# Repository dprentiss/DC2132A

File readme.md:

#DC Bench Power Supply#

Project Features:

- Based on Linear Technology's demostration circuit, [DC2132A](http://cds.linear.com/docs/en/lt-journal/LTJournal-V24N2-02-df-BenchSupply-Szolusha.pdf)
- 0 - 24V current limited 0 - 3A 
- [Eurocard](https://en.wikipedia.org/wiki/Eurocard_(printed_circuit_board)) for 3U subrack
- USB current and voltage monitor output

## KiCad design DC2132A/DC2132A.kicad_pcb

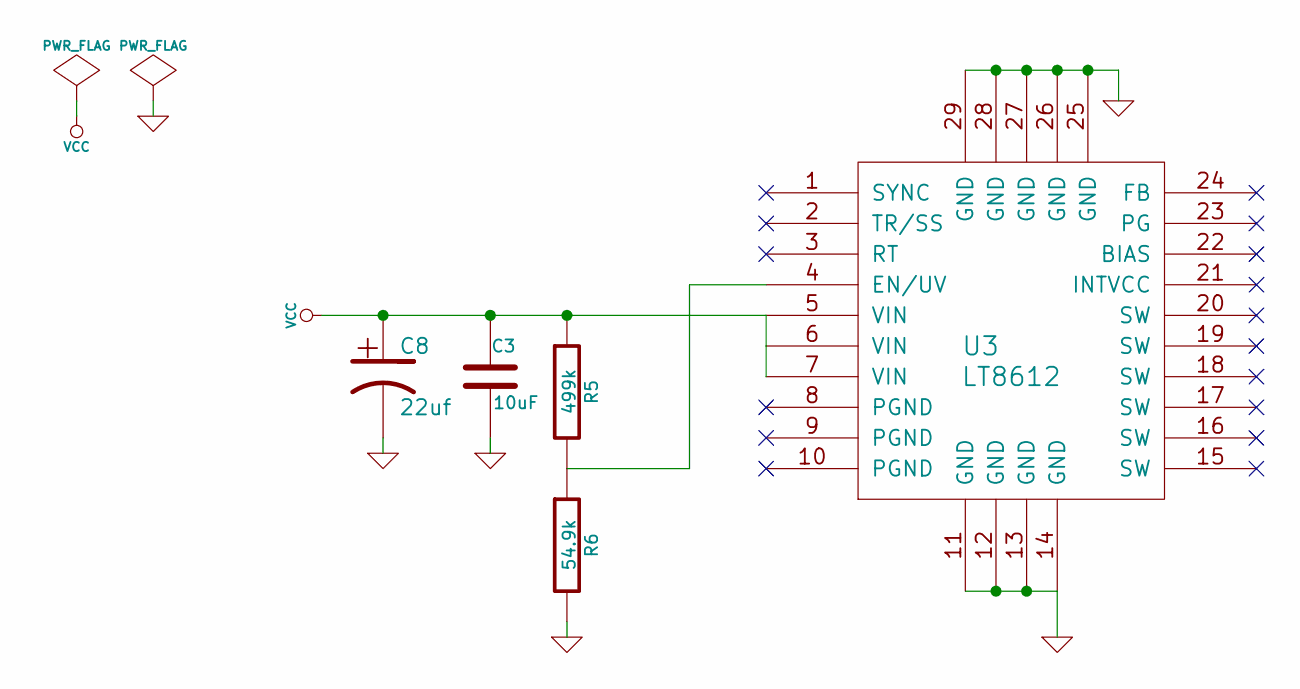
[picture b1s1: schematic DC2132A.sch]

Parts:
C3: 10uF; Rating 50V
C8: 22uf; Rating 63V
R5: 499k
R6: 54.9k
U3: LT8612

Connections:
GND: C3.2, C8.2, R6.2, U3.11 (GND), U3.12 (GND), U3.13 (GND), U3.14 (GND), U3.25 (GND), U3.26 (GND), U3.27 (GND), U3.28 (GND), U3.29 (GND)
unnamed: R5.2, R6.1, U3.4 (EN/UV)
VCC: C3.1, C8.1, R5.1, U3.5 (VIN), U3.7 (VIN)

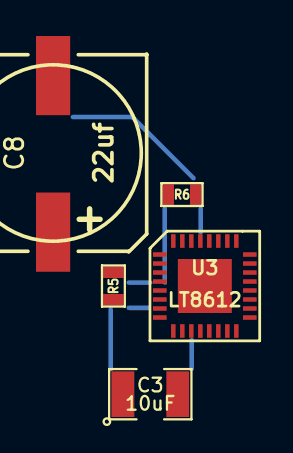
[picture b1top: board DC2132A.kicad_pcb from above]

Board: 2 copper layers, 5 parts (0 on the bottom side), 3 nets.

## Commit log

2015-10-14 :lollipop: Added .gitattributes & .gitignore files
2015-10-14 init readme
2015-10-16 ignore gvim
2015-10-16 project features
2015-10-16 ignore swp
2015-10-20 init picad models
2015-10-21 new kicad version
2015-10-21 added more components from lt schematic
2015-10-21 added pin 6 to TO
2015-10-21 change pin order
